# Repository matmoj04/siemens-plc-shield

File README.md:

# Siemens PLC S7-1215c
Shield for Siemens PLC 1200 line.

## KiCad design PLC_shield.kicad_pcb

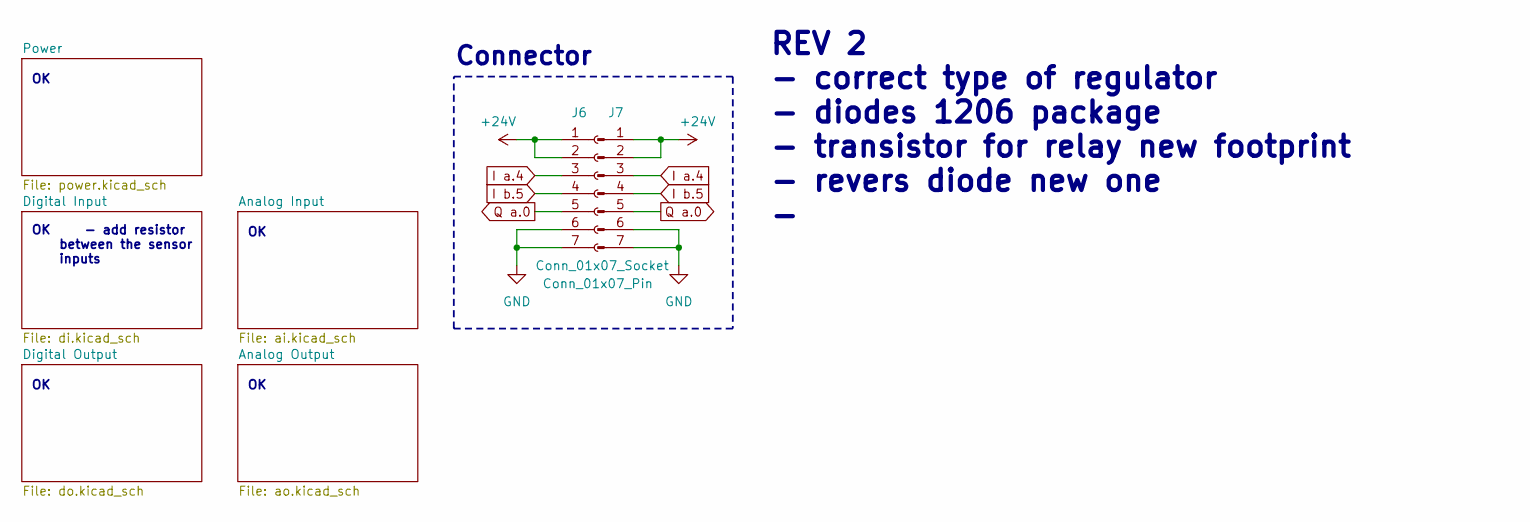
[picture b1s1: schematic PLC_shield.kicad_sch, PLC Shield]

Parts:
J6: Conn_01x07_Socket; PinSocket_1x07_P2.54mm_Horizontal
J7: Conn_01x07_Pin; PinHeader_1x07_P2.54mm_Horizontal

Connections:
+24V: J6.1, J6.2, J7.1, J7.2; also elsewhere on the board
GND: J6.6, J6.7, J7.6, J7.7; also elsewhere on the board
I a.4: J6.3, J7.3; also elsewhere on the board
I b.5: J6.4, J7.4; also elsewhere on the board
Q a.0: J6.5, J7.5; also elsewhere on the board

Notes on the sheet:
REV 2 - correct type of regulator - diodes 1206 package - transistor for relay new footprint - revers diode new one -
Connector
OK - add resistor between the sensor inputs

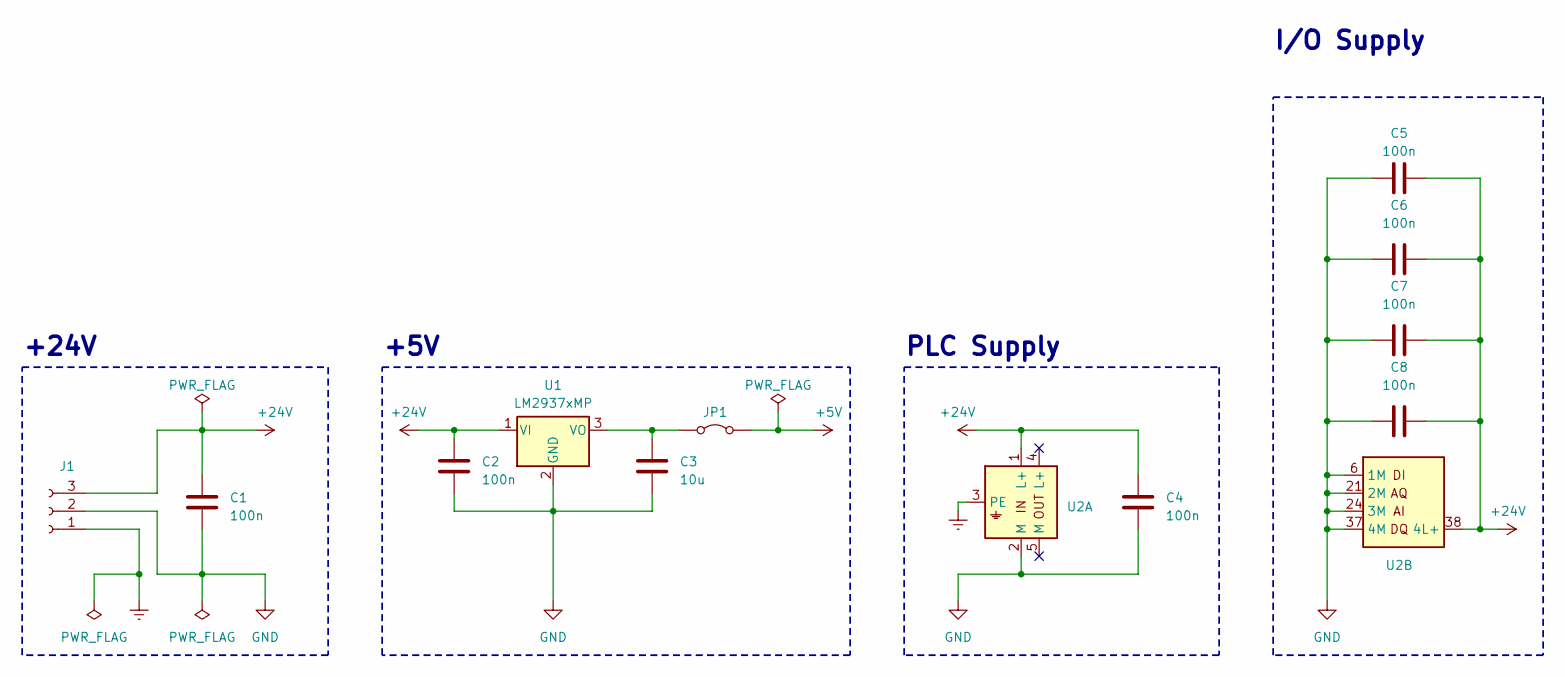
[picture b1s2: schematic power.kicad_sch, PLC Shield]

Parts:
C1, C2, C4, C5, C6, C7, C8: 100n; C_1206_3216Metric_Pad1.33x1.80mm_HandSolder
C3: 10u; C_1206_3216Metric_Pad1.33x1.80mm_HandSolder
J1: Conn_01x03_Socket; DG246-5.08-03P-14-00AH
JP1: Jumper_2_Bridged; PinHeader_1x02_P2.54mm_Vertical
U1: LM2937xMP; SOT-223-3_TabPin2
U2: 1215C

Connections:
+5V: JP1.2 (B); also elsewhere on the board
+24V: C1.1, C2.1, C4.1, C5.2, C6.2, C7.2, C8.2, J1.3, U1.1 (VI), U2.1 (L+), U2.38 (4L+); also elsewhere on the board
Earth: J1.1, U2.3 (PE)
GND: C1.2, C2.2, C3.2, C4.2, C5.1, C6.1, C7.1, C8.1, J1.2, U1.2 (GND), U2.2 (M), U2.6 (1M), U2.21 (2M), U2.24 (3M), U2.37 (4M); also elsewhere on the board
unnamed: C3.1, JP1.1 (A), U1.3 (VO)

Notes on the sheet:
I/O Supply
+5V
+24V
PLC Supply

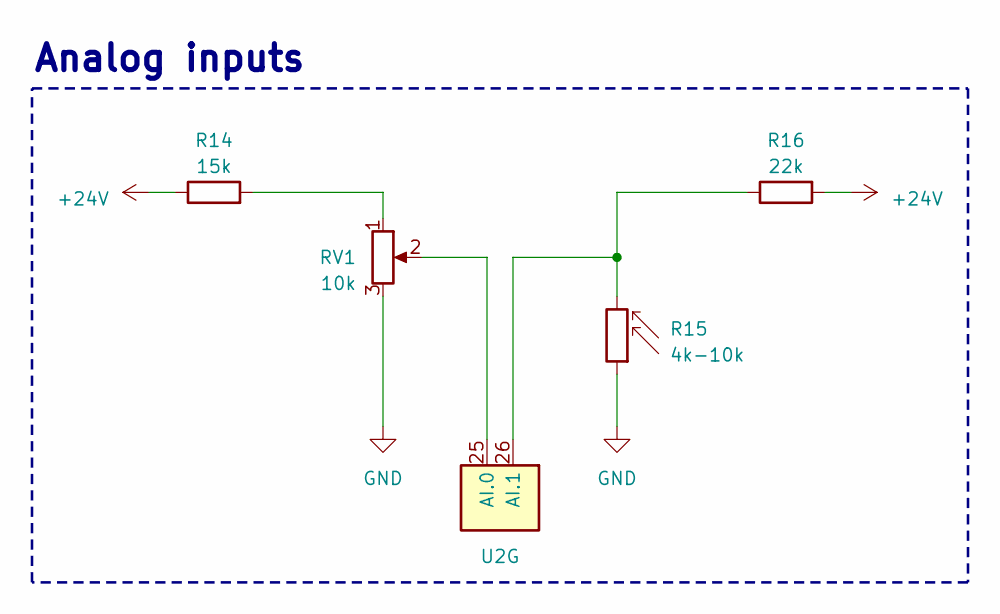
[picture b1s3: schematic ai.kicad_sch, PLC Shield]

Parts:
R14: 15k; R_2010_5025Metric_Pad1.40x2.65mm_HandSolder
R15: 4k-10k; R_LDR_D6.4mm_P3.4mm_Vertical
R16: 22k; R_2010_5025Metric_Pad1.40x2.65mm_HandSolder
RV1: 10k; RK09K1130AV7
U2: 1215C

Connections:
+24V: R14.1, R16.2; also elsewhere on the board
GND: R15.1, RV1.3; also elsewhere on the board
unnamed: R14.2, RV1.1
unnamed: RV1.2, U2.25 (AI.0)
unnamed: R15.2, R16.1, U2.26 (AI.1)

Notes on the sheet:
Analog inputs

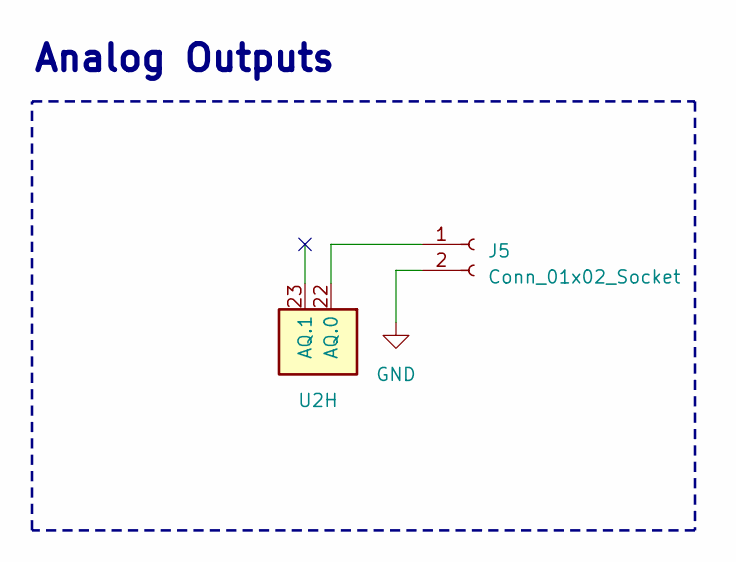
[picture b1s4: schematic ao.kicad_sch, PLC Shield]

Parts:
J5: Conn_01x02_Socket; TerminalBlock_bornier-2_P5.08mm
U2: 1215C

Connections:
GND: J5.2; also elsewhere on the board
unnamed: J5.1, U2.22 (AQ.0)

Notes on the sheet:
Analog Outputs

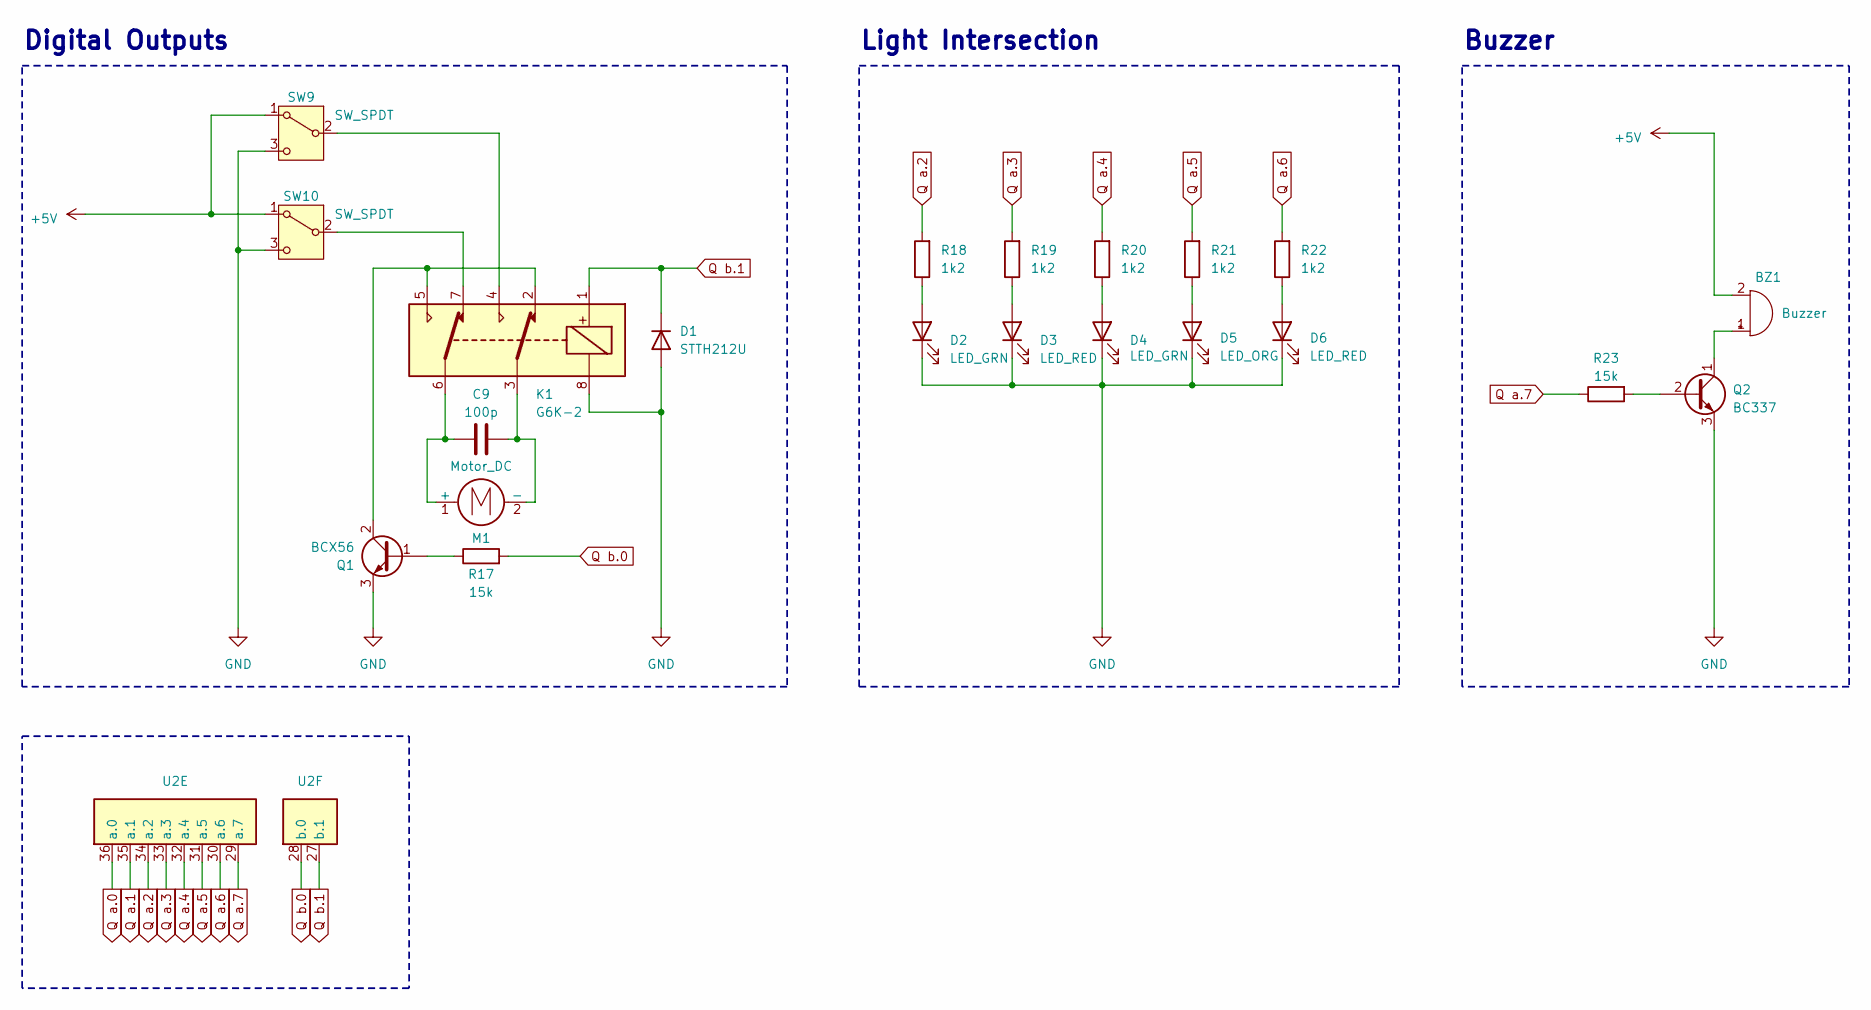
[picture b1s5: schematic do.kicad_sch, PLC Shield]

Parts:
BZ1: Buzzer; Buzzer_12x9.5RM7.6
C9: 100p; C_1206_3216Metric_Pad1.33x1.80mm_HandSolder
D1: STTH212U; D_SMB
D2, D4: LED_GRN; LED_1206_3216Metric_Pad1.42x1.75mm_HandSolder
D3, D6: LED_RED; LED_1206_3216Metric_Pad1.42x1.75mm_HandSolder
D5: LED_ORG; LED_1206_3216Metric_Pad1.42x1.75mm_HandSolder
K1: G6K-2; Relay_DPDT_Omron_G6K-2F-Y
M1: Motor_DC; FIT0491
Q1: BCX56; SOT-89-3
Q2: BC337; TO-92_Inline
R17, R23: 15k; R_2010_5025Metric_Pad1.40x2.65mm_HandSolder
R18, R19, R20, R21, R22: 1k2; R_2010_5025Metric_Pad1.40x2.65mm_HandSolder
SW9, SW10: SW_SPDT; MS4-5L11LSGQ
U2: 1215C

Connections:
+5V: BZ1.2 (-), SW9.1 (A), SW10.1 (A); also elsewhere on the board
GND: D1.2 (A), D2.1 (K), D3.1 (K), D4.1 (K), D5.1 (K), D6.1 (K), K1.8, Q1.3 (E), Q2.3 (E), SW9.3 (C), SW10.3 (C); also elsewhere on the board
unnamed: BZ1.1 (+), Q2.1 (C)
unnamed: D2.2 (A), R18.1
unnamed: D3.2 (A), R19.1
unnamed: D4.2 (A), R20.1
unnamed: D5.2 (A), R21.1
unnamed: D6.2 (A), R22.1
unnamed: C9.2, K1.6, M1.1 (+)
unnamed: C9.1, K1.3, M1.2 (-)
unnamed: Q1.1 (B), R17.1
unnamed: K1.2, K1.5, Q1.2 (C)
unnamed: Q2.2 (B), R23.2
unnamed: K1.4, SW9.2 (B)
unnamed: K1.7, SW10.2 (B)
Q a.0: U2.36 (a.0); also elsewhere on the board
Q a.1: U2.35 (a.1); also elsewhere on the board
Q a.2: R18.2, U2.34 (a.2)
Q a.3: R19.2, U2.33 (a.3)
Q a.4: R20.2, U2.32 (a.4)
Q a.5: R21.2, U2.31 (a.5)
Q a.6: R22.2, U2.30 (a.6)
Q a.7: R23.1, U2.29 (a.7)
Q b.0: R17.2, U2.28 (b.0)
Q b.1: D1.1 (K), K1.1, U2.27 (b.1)

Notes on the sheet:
Light Intersection
Digital Outputs
Buzzer

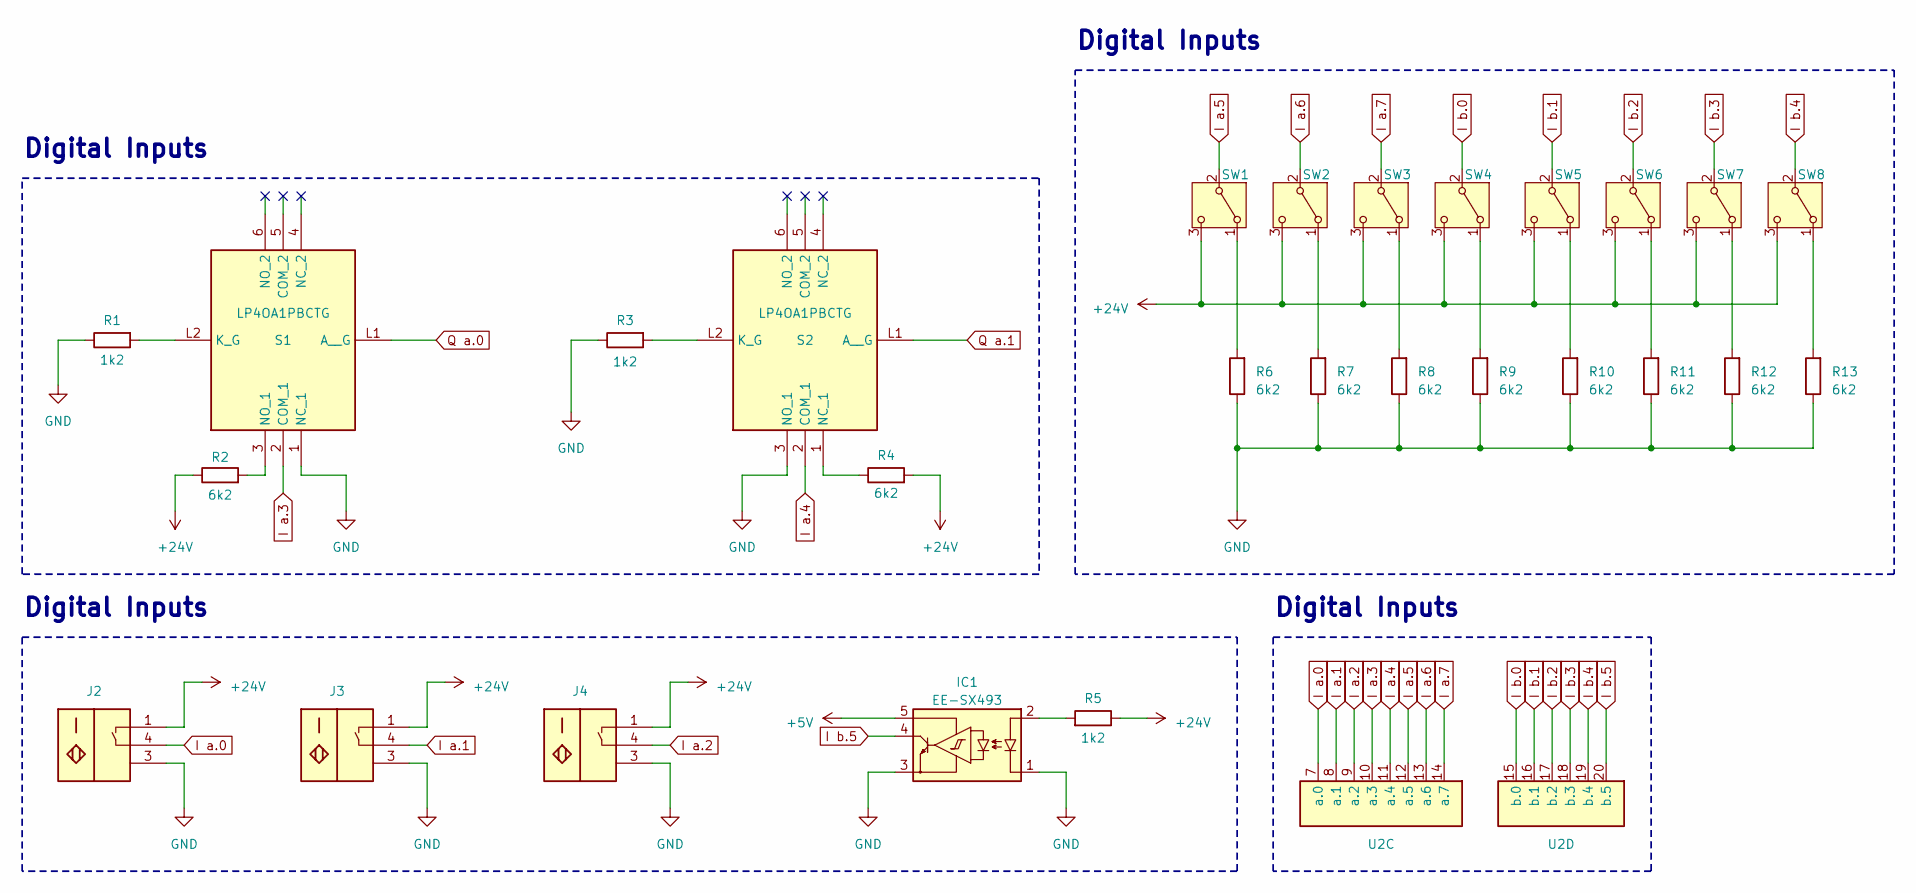
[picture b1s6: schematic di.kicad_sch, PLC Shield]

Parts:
IC1: EE-SX493; EESX493; Manufacturer_Part_Number EE-SX493
J2, J3, J4: T4145015041-001; T4145015051001; Manufacturer_Part_Number T4145015041-001
R1, R3, R5: 1k2; R_2010_5025Metric_Pad1.40x2.65mm_HandSolder
R2, R4, R6, R7, R8, R9, R10, R11, R12, R13: 6k2; R_2010_5025Metric_Pad1.40x2.65mm_HandSolder
S1, S2: LP4OA1PBCTG; Manufacturer_Part_Number LP4OA1PBCTG
SW1, SW2, SW3, SW4, SW5, SW6, SW7, SW8: SW_SPDT; MFP 261 N
U2: 1215C

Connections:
+5V: IC1.5; also elsewhere on the board
+24V: J2.1, J3.1, J4.1, R2.1, R4.2, R5.1, SW1.3 (C), SW2.3 (C), SW3.3 (C), SW4.3 (C), SW5.3 (C), SW6.3 (C), SW7.3 (C), SW8.3 (C); also elsewhere on the board
GND: IC1.1, IC1.3, J2.3, J3.3, J4.3, R1.1, R3.1, R6.1, R7.1, R8.1, R9.1, R10.1, R11.1, R12.1, R13.1, S1.1 (NC_1), S2.3 (NO_1); also elsewhere on the board
I a.0: J2.4, U2.7 (a.0)
I a.1: J3.4, U2.8 (a.1)
I a.2: J4.4, U2.9 (a.2)
I a.3: S1.2 (COM_1), U2.10 (a.3)
I a.4: S2.2 (COM_1), U2.11 (a.4); also elsewhere on the board
I a.5: SW1.2 (B), U2.12 (a.5)
I a.6: SW2.2 (B), U2.13 (a.6)
I a.7: SW3.2 (B), U2.14 (a.7)
I b.0: SW4.2 (B), U2.15 (b.0)
I b.1: SW5.2 (B), U2.16 (b.1)
I b.2: SW6.2 (B), U2.17 (b.2)
I b.3: SW7.2 (B), U2.18 (b.3)
I b.4: SW8.2 (B), U2.19 (b.4)
I b.5: IC1.4, U2.20 (b.5); also elsewhere on the board
unnamed: IC1.2, R5.2
unnamed: R1.2, S1.L2 (K_G)
unnamed: R2.2, S1.3 (NO_1)
unnamed: R3.2, S2.L2 (K_G)
unnamed: R4.1, S2.1 (NC_1)
unnamed: R6.2, SW1.1 (A)
unnamed: R7.2, SW2.1 (A)
unnamed: R8.2, SW3.1 (A)
unnamed: R9.2, SW4.1 (A)
unnamed: R10.2, SW5.1 (A)
unnamed: R11.2, SW6.1 (A)
unnamed: R12.2, SW7.1 (A)
unnamed: R13.2, SW8.1 (A)
Q a.0: S1.L1 (A__G); also elsewhere on the board
Q a.1: S2.L1 (A__G); also elsewhere on the board

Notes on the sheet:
Digital Inputs

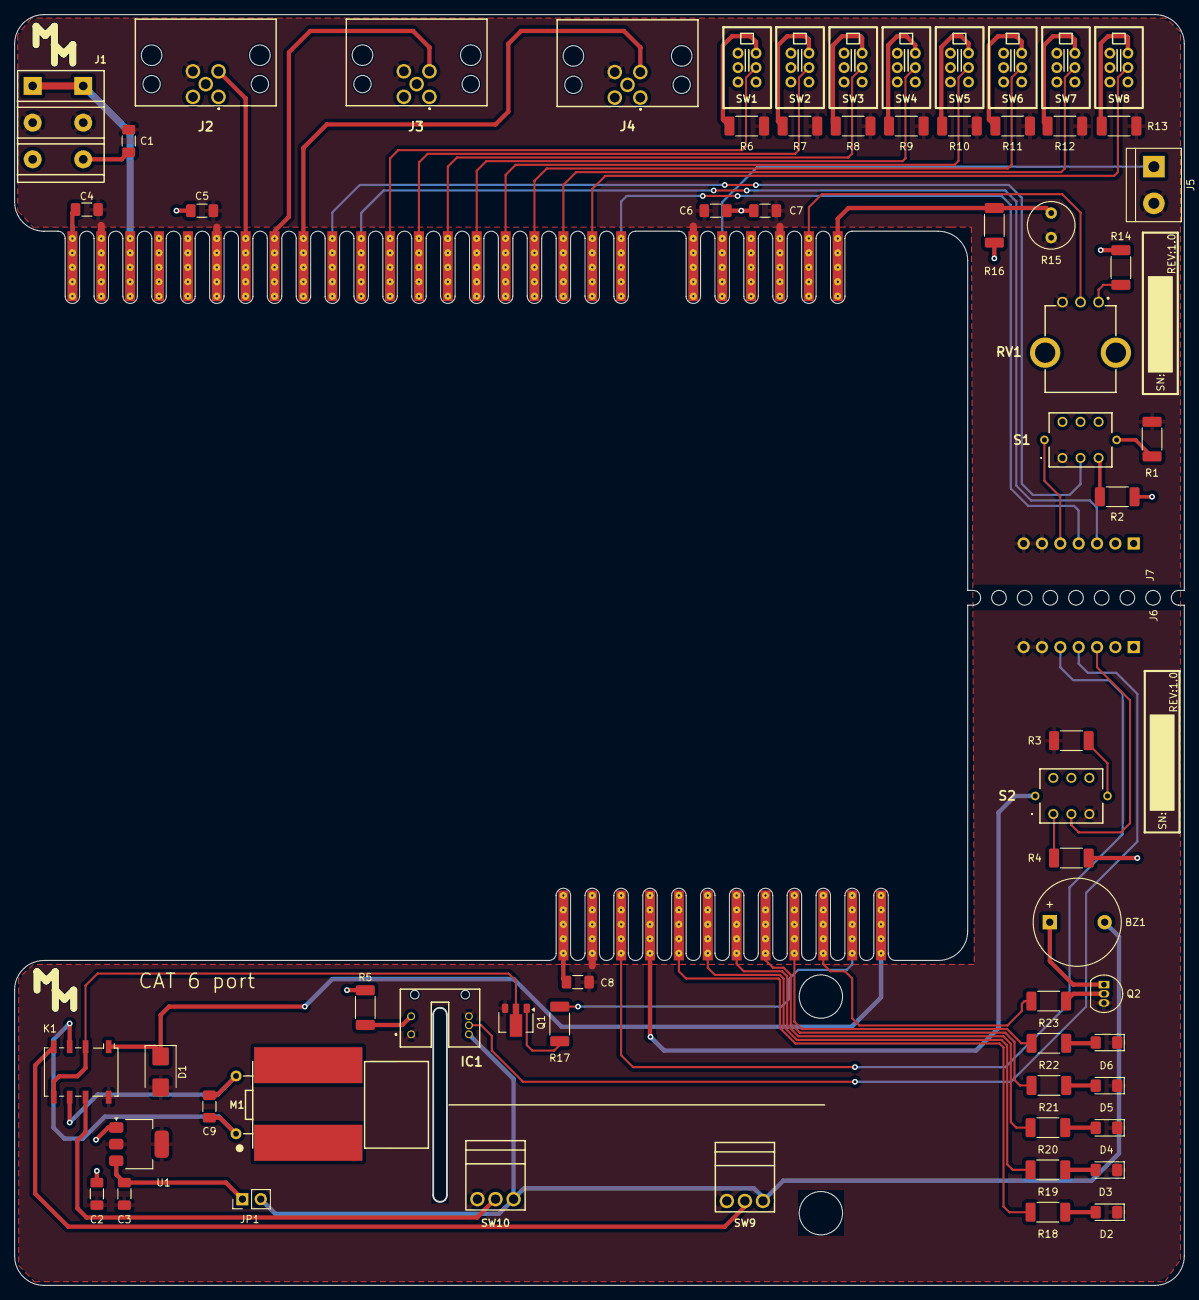
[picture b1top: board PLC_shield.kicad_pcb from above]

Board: 2 copper layers, 161.9 x 175.9 mm, 67 parts (0 on the bottom side), 59 nets.

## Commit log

2024-09-17 Update LICENSE
